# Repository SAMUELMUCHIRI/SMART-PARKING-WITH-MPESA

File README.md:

# SMART PARKING WITH MPESA

## Objective
The fundamental objective of this Project is to familiarize  with the principles of 
engineering design thinking, a process through which a holistic solution is conceived to address tangible, 
real-world issues. 

## The Project is divided into 
- [Hardware Design](#hardware-design)
- [Hardware Programming](#hardware-programming)
- [Database Design](#database-design)
- [Application Design](#application-design) 

## **Hardware Design**
The Components used were 
- NodeMCU ESP8266
- 5 IR sensors
- 1 servo motor
- 1 Capacitor
- Connecting cables
- Power Sockets
- Buck Converter
- Mounting frame
<br>

The components use above were incorporated into a Printed Circuit Board(pcb) .Kicad software was used to design the pcb.

**Geber File**

<br>

**Schematic**

<br>

**Routings**

<br>

**3D View**

<br>
**Developed PCB**

## **Hardware Programming**
The sketch Primary operation contains all the code for the hardware .
The code entail 
- LCD display

```arduino
//Check the whole code this is a snippet
  Wire.begin(I2C_SDA, I2C_SCL);

  lcd.init();  
  lcd.backlight();
  lcd.setCursor(0, 0);
  lcd.print(" SMART PARKING ");

```
- Getting Values from IR sensors
```arduino
//Check the whole code this is a snippet
  int sensorValue1 = digitalRead(EntryPin);
  int sensorValue2 = digitalRead(ExitPin);
  int sensorValue3 = digitalRead(irSensorPin1);
  int sensorValue4 = digitalRead(irSensorPin2);
  int sensorValue5 = digitalRead(irSensorPin3);
  int sensorValue6 = digitalRead(irSensorPin4);

```
- Turning the servo
```arduino
//Check the whole code this is a snippet
void OpenBarrier()
{
  for (int i = 40; i < 180; i++) 
  {
  myservo.write(i); 
  delay(30);                 
  }
  delay(100);
  
  for (int i = 179; i > 40 ; i--) 
  {
  myservo.write(i); 
  delay(30);                 
  }

  delay(30);
}
```
- Connecting the Node Mcu to wifi
```arduino
//Check the whole code this is a snippet
  WiFi.begin(ssid, password);
  lcd.setCursor(0, 0);
  lcd.print("Connecting to ");
  lcd.setCursor(0, 2);
  lcd.print(ssid);
    // Loop continuously while WiFi is not connected
  while (WiFi.status() != WL_CONNECTED)
  {
    delay(100);
    lcd.setCursor(0 ,3);
    lcd.print("scanning.....");
  }
  delay(200);
  lcd.clear();
  // Connected to WiFi
  //Serial.println();

    lcd.setCursor(0, 3);
  lcd.print(WiFi.localIP());
    lcd.setCursor(0, 1);
  lcd.print("Connected!  ");
  delay(250);
  lcd.clear();
  
```
- Connecting the NodeMcu to Local host (can be changed)
```arduino
//Check the whole code this is a snippet
WiFiClient client;

  if (!client.connect(serverIP, serverPort)) {
    lcd.clear();
    lcd.setCursor(0 , 1);
    lcd.print("NO LOCALHOST");
    //Serial.println("Connection failed");
    lcd.setCursor(5 , 2);
    lcd.print("WRONG SERVERIP");
    lcd.setCursor(3 , 3);
    lcd.print(serverIP);
    delay(1000);
    lcd.setCursor(0 , 1);
    lcd.clear();
  }
```
- Transmitting sensor data from Node Mcu to Local host
```arduino
//Check the whole code this is a snippet
  String postData = "sendval1=" + String(sensorValue3) +
                    "&sendval2=" + String(sensorValue4) +
                    "&sendval3=" + String(sensorValue5) +
                    "&sendval4=" + String(sensorValue6);

  client.println("POST /index.php HTTP/1.1");
  client.print("Host: ");
  client.println(serverIP);
  client.println("Content-Type: application/x-www-form-urlencoded");
  client.print("Content-Length: ");
  client.println(postData.length());
  client.println("Connection: close");
  client.println();
  client.println(postData);
```
- Notify any errors encountered in any operation and how to solve them

## **Database Design**
 MySQL was used as the DBMS
The ER diagram is Shown Below

## **Application Design**
The web app was wtitten in php .Queries are sent to the database as the user interacts with the application.
```php

<?php
//connction to the Database dbconnect.php

            $host="localhost";
            $dbname="smart_parking";
            $username="root";
            $password= "";
            $conn=mysqli_connect(hostname: $host,
                                    username: $username,    
                                    password: $password , 
                                    database: $dbname);
            if(mysqli_connect_errno()){
                die("Connection Error". mysqli_connect_error());}
            //echo"Database Online";

?>
```
 <br>

 ```php
 //logging in data sent by the NodeMCU to the data_log.txt
       if ($_SERVER["REQUEST_METHOD"] == "POST") {
                    $data = array(
                      'sendval1' => $_POST['sendval1'],
                      'sendval2' => $_POST['sendval2'],
                      'sendval3' => $_POST['sendval3'],
                      'sendval4' => $_POST['sendval4']
                    );
                  
                    $jsonContent = json_encode($data, JSON_PRETTY_PRINT);
                    $logFile = "data_log.txt";
                    file_put_contents($logFile, $jsonContent);
                  
                    echo "Values uploaded successfully to data_log.txt";
                  }
 ```
 <br>

 ```php
 //storing contents of the log file to Database
$fileContent = file_get_contents("data_log.txt");
                    if ($fileContent !== false) {
                      $decodedData = json_decode($fileContent, true);
                      if ($decodedData) {
                        $IR1=$decodedData['sendval1'];
                        $IR2=$decodedData['sendval2'];
                        $IR3=$decodedData['sendval3'];
                        $IR4=$decodedData['sendval4'];

                        //$sql = "INSERT INTO system_status (IR1, IR2 , IR3 ,IR4 ) VALUES ($IR1 ,$IR2 , $IR2 ,$IR4)";
                        $sql="UPDATE system_status SET IR1=$IR1,IR2=$IR2,IR3=$IR3,IR4=$IR4" ;
                    
                        if ($conn->query($sql) === TRUE) {
                            echo "<br>";
        
                        //echo "Data inserted successfully";
                        } else {
                            echo "<br>";
                        echo "Error: " . $sql . "<br>" . $conn->error;
                        
                    }
                      }
                    }

 ```

<br>

```php
//Fetch values from Database 
                
                $query1 = "select IR1 FROM system_status ;";
                $query2 = "select IR2 FROM system_status ;";
                $query3 = "select IR3 FROM system_status ;";
                $query4 = "select IR4 FROM system_status ;";
                $result1 = $conn->query( $query1 );
                $result2 = $conn->query( $query2 );
                $result3 = $conn->query( $query3 );
                $result4 = $conn->query( $query4 );
                $slot1 =$result1->fetch_assoc();
                $slot2 =$result2->fetch_assoc();
                $slot3 =$result3->fetch_assoc();
                $slot4 =$result4->fetch_assoc();
```
```php
//the following lines of code compare values from current database value to previous database values and assigns either empty or full slot
                
                if(stripslashes($slot1['IR1'])== 0){
                    echo" SLOT 1 : FULL";
                    if((stripslashes($slot11['IR1'])== 1) and ($IR1==0)){
                        $date_time = date("Y-m-d H:i:s"); 
                        $current_date_time=strval($date_time);
                        $query5="UPDATE parking_details SET Time_In = '$current_date_time'  WHERE Parking_Number =1";
                        $conn->query($query5);

                    }else{
                 
                    }
                    
                }else{
                    echo"SLOT 1 :EMPTY";
                    if((stripslashes($slot11['IR1'])== 0) and ($IR1==1)){
                        $date_time = date("Y-m-d H:i:s"); 
                        $current_date_time=strval($date_time);
                        $query5="UPDATE parking_details SET Time_Out = '$current_date_time' WHERE Parking_Number =1";
                        $conn->query($query5);
                    } else{
                   }}
```
 Here's the landing Homepage

<br>

**Payment** as an integral part of the project was realized using the [**DarajaAPI**](https://developer.safaricom.co.ke/)
The Client Receives an STK push on the phone an is billed accordingly.The Payment system is able to validate transactions
the Following files are for payment
- stkpush.php
- payment.php

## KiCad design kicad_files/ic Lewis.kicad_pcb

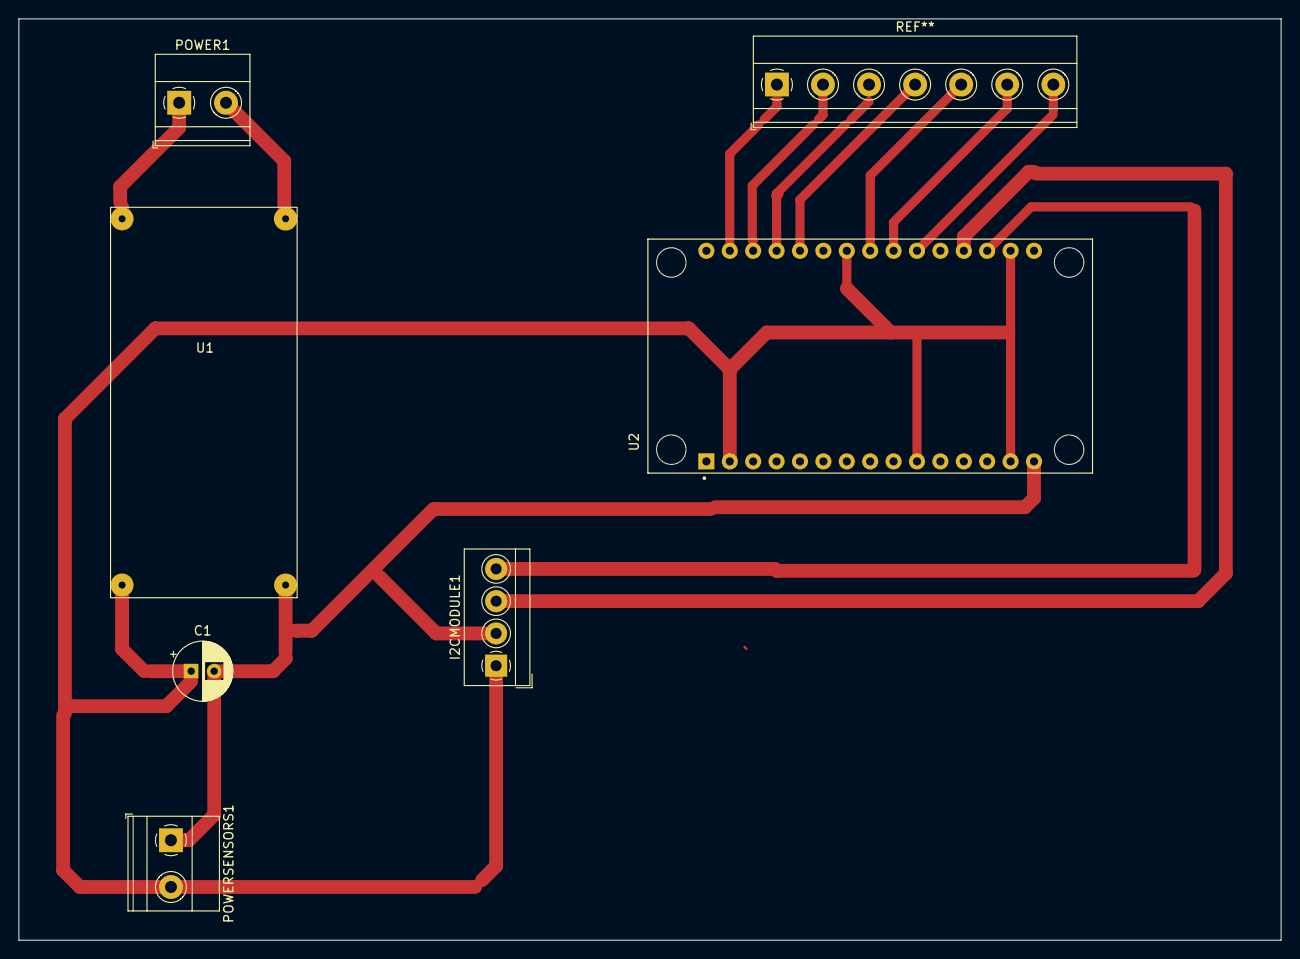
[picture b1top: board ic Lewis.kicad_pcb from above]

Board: 2 copper layers, 137.0 x 100.0 mm, 6 parts (0 on the bottom side), 2 nets.

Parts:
C1: 10u; CP_Radial_D6.3mm_P2.50mm
I2CMODULE1: I2C_module; TerminalBlock_4Ucon_1x04_P3.50mm_Horizontal
POWER1: Screw_Terminal_01x02; TerminalBlock_Phoenix_MKDS-1,5-2-5.08_1x02_P5.08mm_Horizont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
POWERSENSORS1: Screw_Terminal_01x02; TerminalBlock_Phoenix_MKDS-1,5-2-5.08_1x02_P5.08mm_Horizont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
U1: Buck; testesp
U2: NodeMcu_Esp8266; MODULE_ZC563900

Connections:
GND: C1.1, POWERSENSORS1.2
unnamed: C1.2, POWERSENSORS1.1

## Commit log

2023-10-24 First of many
2023-11-08 First Working model
2023-11-10 Intergrated the database
2023-11-12 building the physical system
2023-11-17 basic operation
2023-11-17 best efforts tbh
2023-11-21 bug fixes
2023-11-24 Mpesa Intergration Check
2023-11-25 able to record in and out times and dispaly
2023-11-27 Final SQL queries
2024-01-05 Organize 1.0.0
2024-01-05 test
2024-01-05 uploading images
2024-01-05 small changes
2024-01-05 embedding images
2024-01-05 adding er image
2024-01-05 adding an image
2024-01-05 major changes
2024-01-05 Final touches
2024-01-05 small additions
2024-01-06 removing spelling mistakes
2024-11-27 added pcb files
2025-08-20 file restructure
2025-08-20 file changes and landing page
2025-09-05 updating routes an 404 error page
